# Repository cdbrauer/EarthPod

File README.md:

# EarthPod
Code for the [EarthPod](https://cdbrauer.github.io/research/index.html#earthpod) environmental sensor pod.

## Datalogging-Arduino

### Hardware

The code in this folder is intended to be used in a sensor pod based on a Adafruit Feather M0 Adalogger. Connected sensors include:

| Sensor | [V1](https://github.com/cdbrauer/EarthPod/tree/master/Datalogging-Arduino/feather-sensor-logging-v1) | [V2](https://github.com/cdbrauer/EarthPod/tree/master/Datalogging-Arduino/feather-sensor-logging-v2.1) |
| :------------- | :----------: | :-----------: |
| RTC | DS3231 | DS3231 |
| Gyroscope | FXAS21002C | FXAS21002C |
| Acclerometer/Magnetometer | FXOS8700 | FXOS8700 |
| Temperature/Humidity | si7021 | SHT21 |
| Air Pressure/Temperature | BME280 | BMP280 or SPL06-007 |
| Light Level | SI1145 | BH1750 |
| Wind Direction | TCS34725 | N/A |
| Wind Speed | Handheld Anemometer | N/A |

### feather-sensor-logging-v1

*Compatible with V1 only*

This program will create a .csv file on the Adalogger's SD card that records the measurements captured by the sensors. This program is only compatible with the Adafruit Feather M0 Adalogger, and will not fit on the Adafruit Feather 32u4 Adalogger due to memory constraints.

### feather-sensor-logging-v2.1

*Compatible with V2 Only*

This program will create a .csv file on the Adalogger's SD card that records the measurements captured by the sensors. This program is only compatible with the Adafruit Feather M0 Adalogger, and will not fit on the Adafruit Feather 32u4 Adalogger due to memory constraints.

### feather-sensor-tests/SPL06-007

Test I2C communication for an SPL06-007 air pressure and temperature sensor.

### feather-sensor-tests/anemometer

Test initialization and interrupts for a wind speed sensor from a [handheld anemometer](https://www.amazon.com/Anemometer-Velocity-Measurement-Thermometer-Windsurfing/dp/B01JOTJMU6/).

## Datalogging-Python

### Hardware

The code in this folder is intended to be used in a sensor pod based on a Raspberry Pi or Google Coral. The primary
sensing hardware is the Coral Environmental Sensor Board, which provides ambient light, barometric pressure, humidity, and temperature measurements. This board is compatible with both the Google Coral and Raspberry Pi. Additional sensors can be connected to the Environmental Sensor Board through a series of Grove connectors.

### enviro\_logging.py

This program will create a .csv file that records the measurements captured by the sensors in the Environmental Sensor
Board.

### enviro\_logging\_wind.py

This program adds functionality for reading wind speed using the sensor from a [handheld anemometer](https://www.amazon.com/Anemometer-Velocity-Measurement-Thermometer-Windsurfing/dp/B01JOTJMU6/).

### enviro\_logging\_wind\_airflow.py

This program adds functionality for reading wind speed using a [F662 Board Mount Airflow Sensor](https://www.degreec.com/pages/f660-662) from Degree Controls.

## MagnetRelease

### MagnetRelease.ino

Arduino program for the twist-release magnet system used to deploy the pod.

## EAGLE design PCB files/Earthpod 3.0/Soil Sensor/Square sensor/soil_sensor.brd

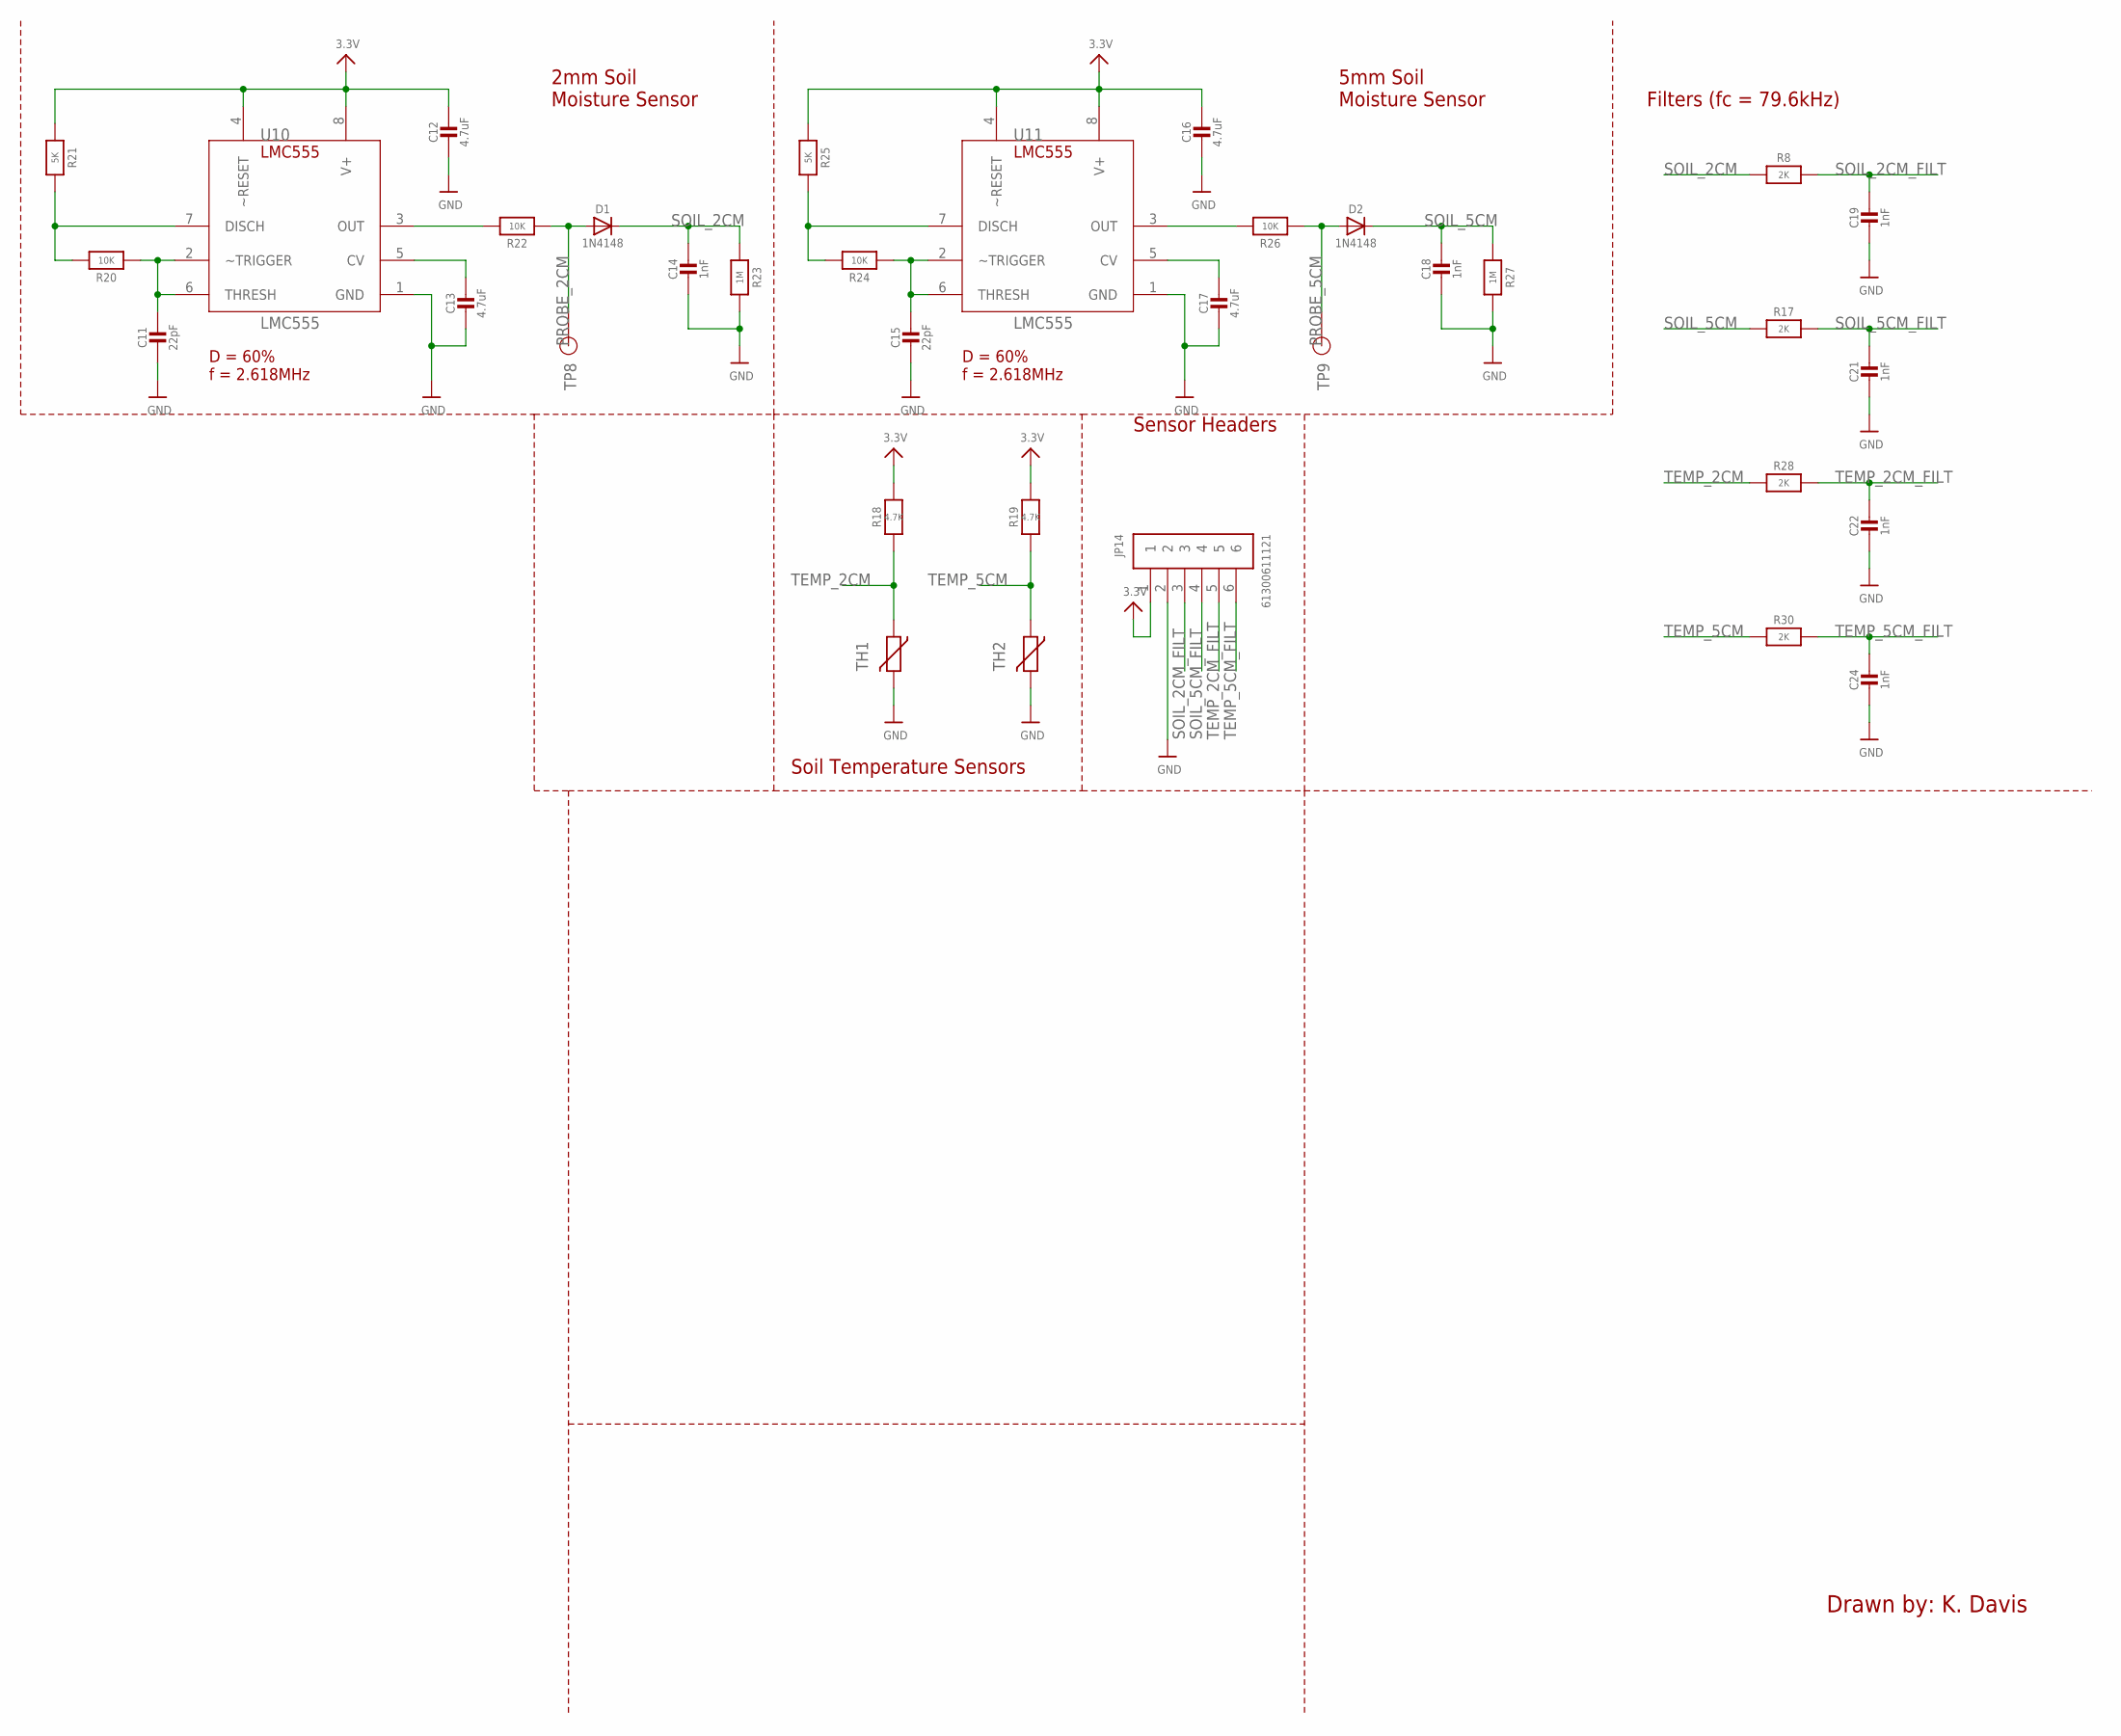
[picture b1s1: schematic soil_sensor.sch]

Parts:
C11, C15: 22pF; 0805-NO
C12, C13, C16, C17: 4.7uF; 0805-NO
C14, C18, C19, C21, C22, C24: 1nF; 0805-NO
D1, D2: 1N4148; SOD-323
JP14: 61300611121
R8, R17, R28, R30: 2K; 0603-NO
R18, R19: 4.7K; 0805-NO
R20, R22, R24, R26: 10K; 0805-NO
R21, R25: 5K; 0805-NO
R23, R27: 1M; 0805-NO
TH1, TH2: VARISTORCN1206; CT/CN1206
TP8, TP9: TP; TP_50MIL_CIRC
U10, U11: LMC555; SOIC-8

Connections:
3.3V: C12.1, C16.1, JP14.1, R18.2, R19.2, R21.1, R25.1, U10.4 (~RESET), U10.8 (V+), U11.4 (~RESET), U11.8 (V+)
FGD: C11.2, C12.2, C13.2, C14.2, C15.2, C16.2, C17.2, C18.2, C19.2, C21.2, C22.2, C24.2, JP14.2, R23.2, R27.2, TH1.2, TH2.2, U10.1 (GND), U11.1 (GND)
unnamed: C11.1, R20.1, U10.2 (~TRIGGER), U10.6 (THRESH)
unnamed: R20.2, R21.2, U10.7 (DISCH)
unnamed: C13.1, U10.5 (CV)
unnamed: C15.1, R24.1, U11.2 (~TRIGGER), U11.6 (THRESH)
unnamed: R24.2, R25.2, U11.7 (DISCH)
unnamed: R22.2, U10.3 (OUT)
unnamed: C17.1, U11.5 (CV)
unnamed: R26.2, U11.3 (OUT)
PROBE_2CM: D1.A, R22.1, TP8.1
PROBE_5CM: D2.A, R26.1, TP9.1
SOIL_2CM: C14.1, D1.C, R8.1, R23.1
SOIL_2CM_FILT: C19.1, JP14.3, R8.2
SOIL_5CM: C18.1, D2.C, R17.1, R27.1
SOIL_5CM_FILT: C21.1, JP14.4, R17.2
TEMP_2CM: R18.1, R28.1, TH1.1
TEMP_2CM_FILT: C22.1, JP14.5, R28.2
TEMP_5CM: R19.1, R30.1, TH2.1
TEMP_5CM_FILT: C24.1, JP14.6, R30.2

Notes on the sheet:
Soil Temperature Sensors
2mm Soil Moisture Sensor
5mm Soil Moisture Sensor
Filters (fc = 79.6kHz)
Drawn by: K. Davis
D = 60% f = 2.618MHz
Sensor Headers

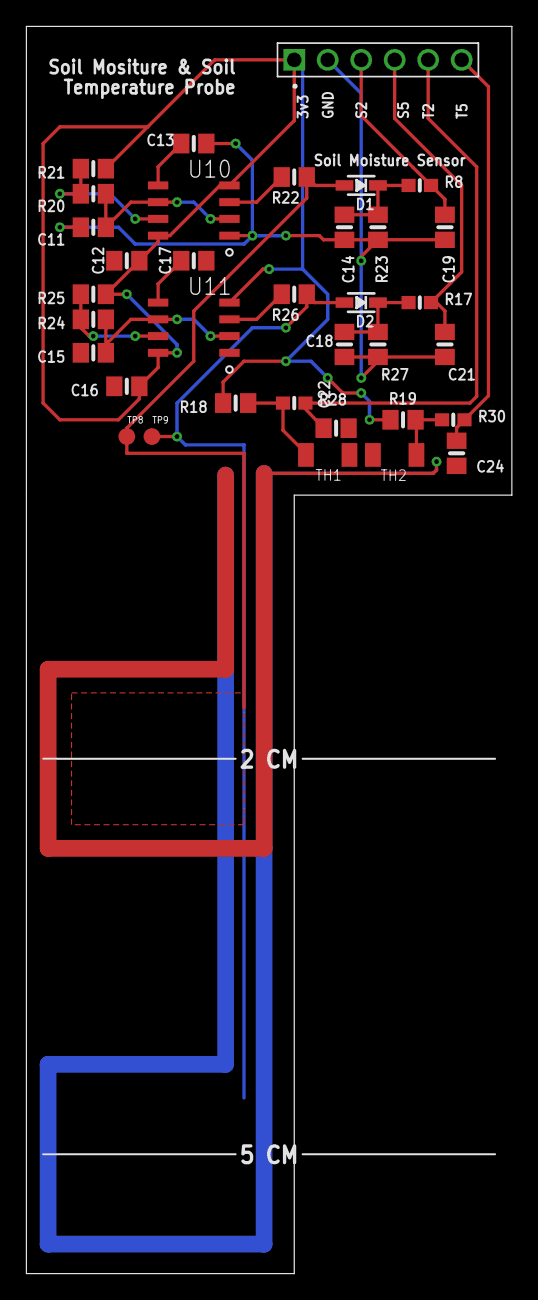
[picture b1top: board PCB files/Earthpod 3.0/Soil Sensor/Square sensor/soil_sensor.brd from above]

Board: 2 copper layers, 36.8 x 94.6 mm, 35 parts (0 on the bottom side), 20 nets.

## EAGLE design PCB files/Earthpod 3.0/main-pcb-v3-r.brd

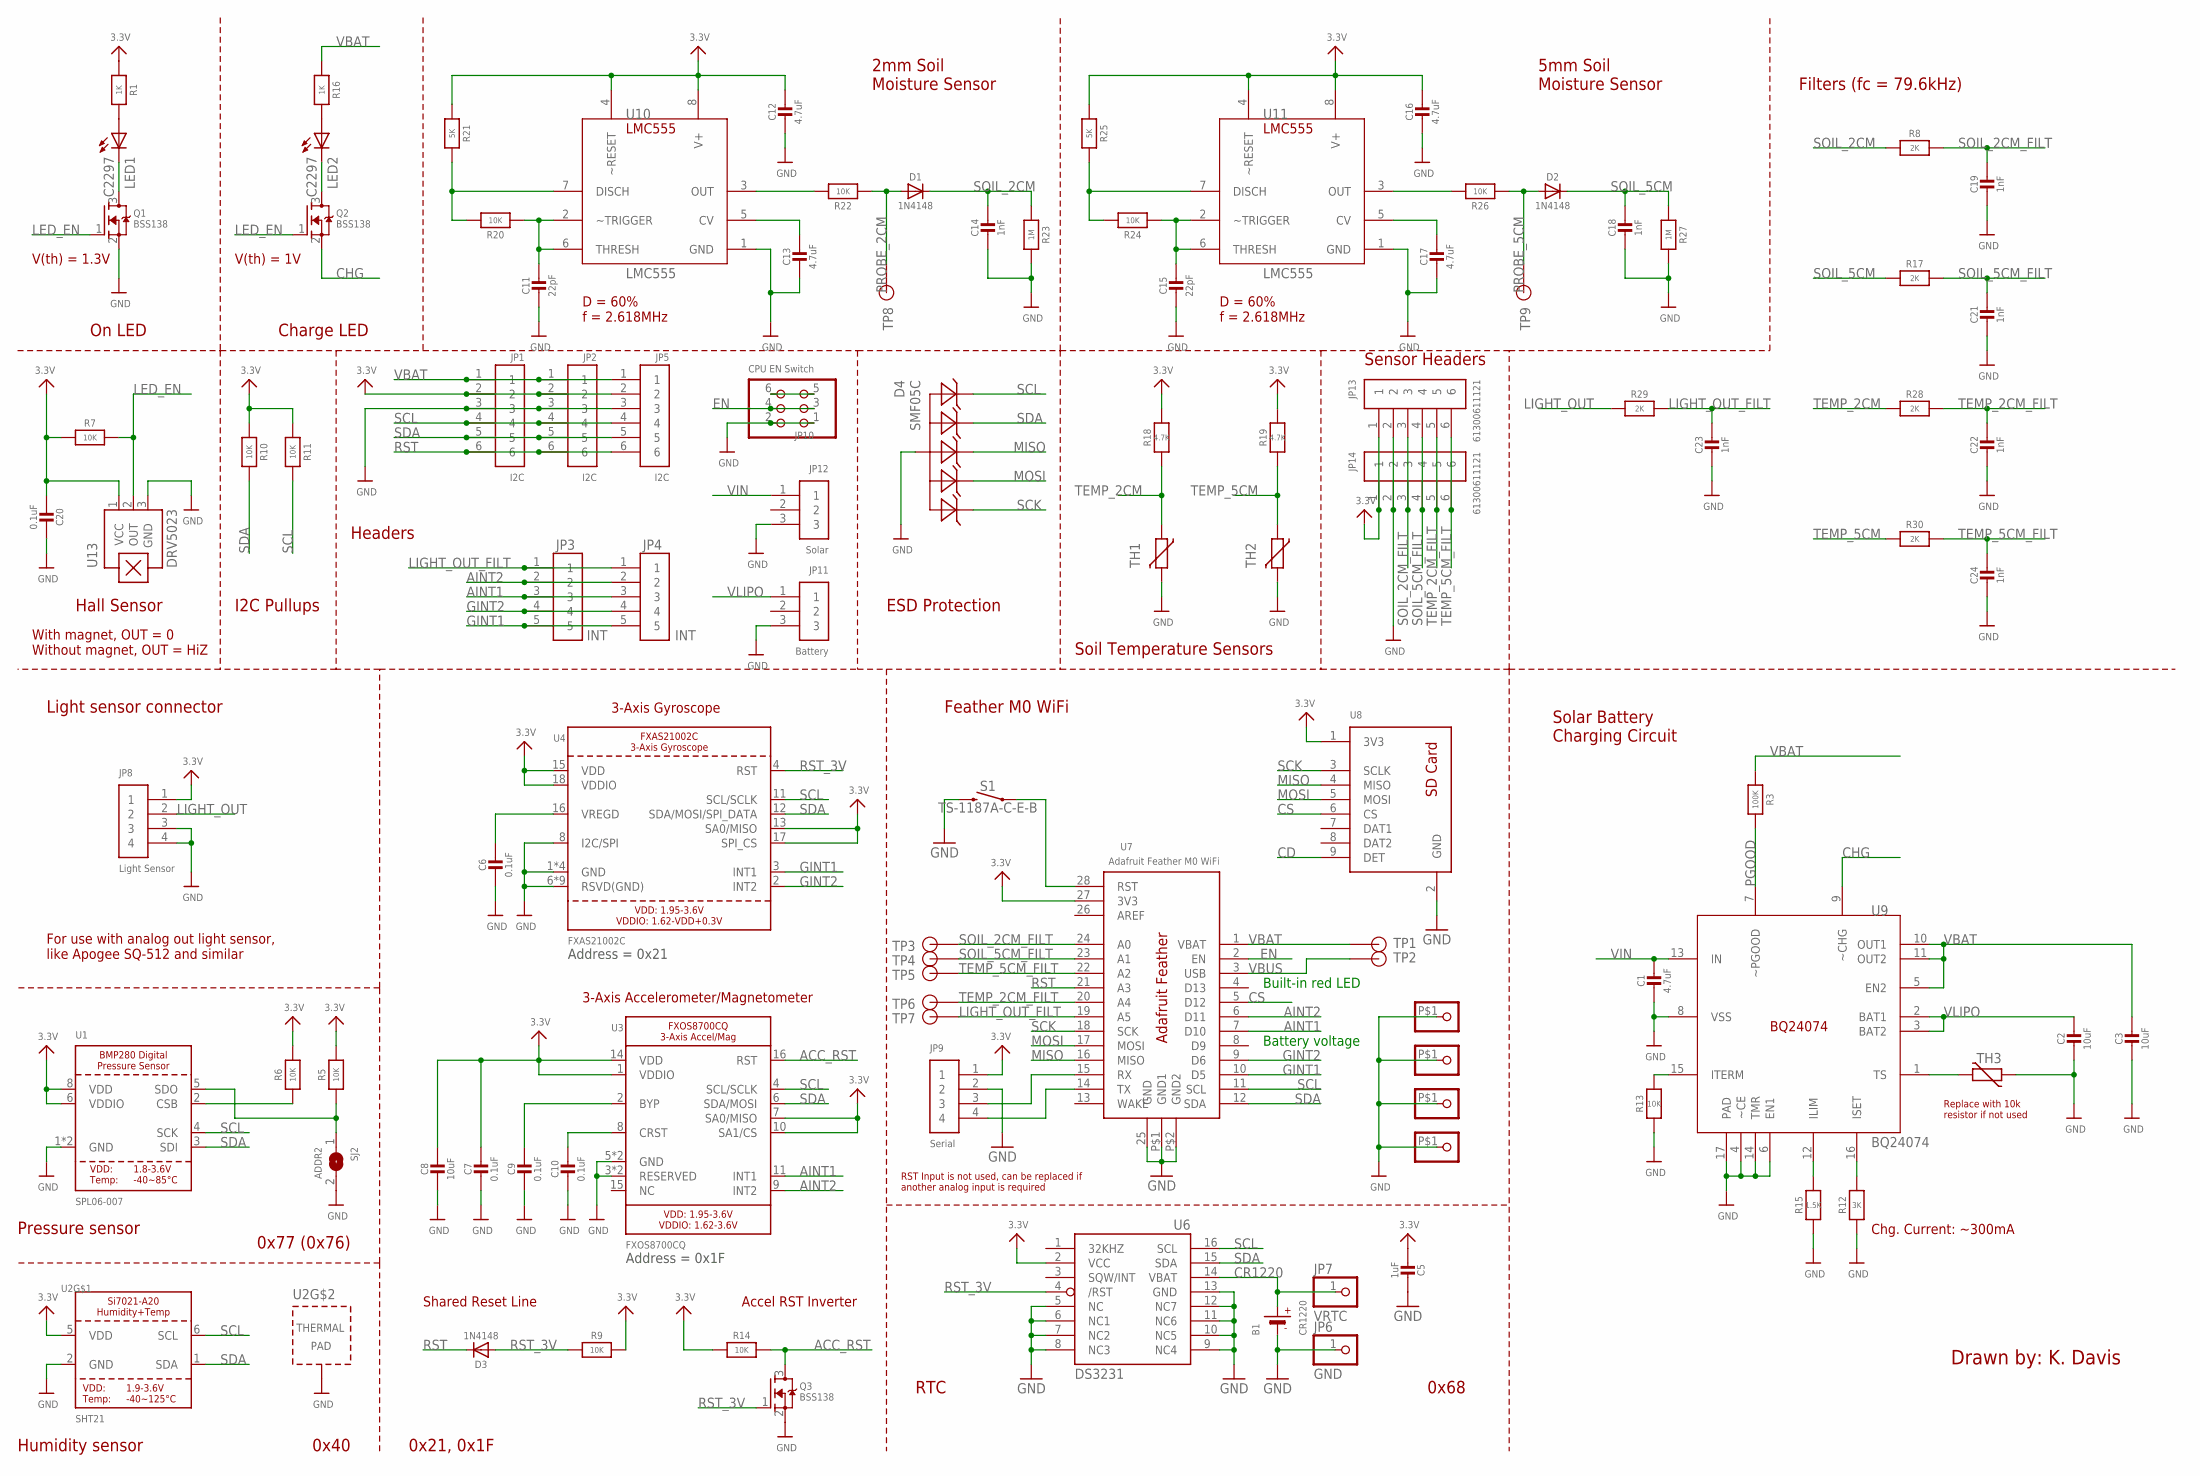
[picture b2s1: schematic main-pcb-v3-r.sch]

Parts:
B1: CR1220; CR1220-2
C1, C12, C13, C16, C17: 4.7uF; 0805-NO
C2, C3, C8: 10uF; 0805-NO
C5: 1uF; 0805-NO
C6, C7, C9, C10, C20: 0.1uF; 0805-NO
C11, C15: 22pF; 0805-NO
C14, C18, C19, C21, C22, C23, C24: 1nF; 0805-NO
D1, D2, D3: 1N4148; SOD-323
D4: SMF05C; SC70-6
JP1, JP2, JP5: I2C; 61300611121
JP3, JP4: INT; 61300511121
JP6: GND; 1X01_ROUND
JP7: VRTC; 1X01_ROUND
JP8: Light Sensor; 61300411121
JP9: Serial; 61300411121
JP10: CPU EN Switch; 2X03
JP11: Battery; 61300311121
JP12: Solar; 61300311121
JP13, JP14: 61300611121
LED1, LED2: C2297; CHIPLED_0805
Q1, Q2, Q3: BSS138; SOT23-WIDE
R1, R16: 1K; 0603-NO
R3: 100K; 0603-NO
R5, R6, R7, R10, R11: 10K; 0603-NO
R8, R17, R28, R29, R30: 2K; 0603-NO
R9, R13, R14, R20, R22, R24, R26: 10K; 0805-NO
R12: 3K; 0805-NO
R15: 1.5K; 0805-NO
R18, R19: 4.7K; 0805-NO
R21, R25: 5K; 0805-NO
R23, R27: 1M; 0805-NO
S1: TS-1187A-C-E-B; TACTILE_SWITCH_SMD_5.2MM
SJ2: ADDR2; SOLDERJUMPER_ARROW_NOPASTE
TH1, TH2, TH3: VARISTORCN1206; CT/CN1206
TP1, TP2, TP3, TP4, TP5, TP6, TP7, TP8, TP9: TP; TP_50MIL_CIRC
U1: SPL06-007; BMX280_COMBO
U2: SHT21; DFN6_3X3_SI
U3: FXOS8700CQ; QFN16_3MM_FREESCALE_5X3
U4: FXAS21002C; QFN24_4MM_FREESCALE_7X5
U6: DS3231/SO; SO16W
U7: Adafruit Feather M0 WiFi; FEATHER
U8: SDCARD2
U9: BQ24074; VQFN-16_3MM
U10, U11: LMC555; SOIC-8
U13: DRV5023; SOT-23
U$1, U$17, U$19, U$21: MOUNTING

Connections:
3.3V: C5.2, C7.1, C8.1, C12.1, C16.1, C20.2, JP1.2, JP2.2, JP5.2, JP8.1, JP9.1, JP13.1, JP14.1, R1.1, R5.2, R6.2, R7.1, R9.2, R10.1, R11.1, R14.1, R18.2, R19.2, R21.1, R25.1, U1.6 (VDDIO), U1.8 (VDD), U2.5 (VDD), U3.1 (VDDIO), U3.7 (SA0/MISO), U3.10 (SA1/CS), U3.14 (VDD), U4.13 (SA0/MISO), U4.15 (VDD), U4.17 (SPI_CS), U4.18 (VDDIO), U6.2 (VCC), U7.27 (3V3), U8.1 (3V3), U10.4 (~RESET), U10.8 (V+), U11.4 (~RESET), U11.8 (V+), U13.1 (VCC)
ACC_RST: Q3.3 (D), R14.2, U3.16 (RST)
AINT1: JP3.3, JP4.3, U3.11 (INT1), U7.7 (D10)
AINT2: JP3.2, JP4.2, U3.9 (INT2), U7.6 (D11)
CD: U8.9 (DET)
CHG: Q2.2 (S), U9.9 (~CHG)
CR1220: B1.+, JP7.1, U6.14 (VBAT)
CS: U7.5 (D12), U8.6 (CS)
EN: JP10.3, JP10.4, U7.2 (EN)
GINT1: JP3.5, JP4.5, U4.3 (INT1), U7.10 (D5)
GINT2: JP3.4, JP4.4, U4.2 (INT2), U7.9 (D6)
GND: B1.-, C1.2, C2.2, C3.2, C5.1, C6.2, C7.2, C8.2, C9.2, C10.2, C11.2, C12.2, C13.2, C14.2, C15.2, C16.2, C17.2, C18.2, C19.2, C20.1, C21.2, C22.2, C23.2, C24.2, D4.2 (A), JP1.3, JP2.3, JP5.3, JP6.1, JP8.3, JP8.4, JP9.2, JP10.1, JP10.2, JP11.3, JP12.3, JP13.2, JP14.2, Q1.2 (S), Q3.2 (S), R12.1, R13.1, R15.1, R23.2, R27.2, S1.3 (2), SJ2.2, TH1.2, TH2.2, TH3.2, U1.1 (GND), U1.7 (GND), U2.2 (GND), U2.PAD (TP), U3.3 (RESERVED), U3.5 (GND), U3.12 (GND), U3.13 (RESERVED), U4.1 (GND), U4.5 (GND), U4.6 (RSVD(GND)), U4.7 (RSVD(GND)), U4.8 (I2C/SPI), U4.9 (RSVD(GND)), U4.10 (RSVD(GND)), U4.14 (GND), U4.19 (GND), U4.20 (RSVD(GND)), U4.21 (RSVD(GND)), U4.22 (RSVD(GND)), U4.23 (RSVD(GND)), U4.24 (RSVD(GND)), U6.5 (NC), U6.6 (NC1), U6.7 (NC2), U6.8 (NC3), U6.9 (NC4), U6.10 (NC5), U6.11 (NC6), U6.12 (NC7), U6.13 (GND), U7.25 (GND), U7.P$1 (GND1), U7.P$2 (GND2), U8.2 (GND), U9.4 (~CE), U9.6 (EN1), U9.8 (VSS), U9.14 (TMR), U9.17 (PAD), U10.1 (GND), U11.1 (GND), U13.3 (GND), U$1.P$1, U$17.P$1, U$19.P$1, U$21.P$1
ITERM: R13.2, U9.15 (ITERM)
LED1: LED1.C, Q1.3 (D)
LED2: LED2.C, Q2.3 (D)
LED_EN: Q1.1 (G), Q2.1 (G), R7.2, U13.2 (OUT)
LIGHT_OUT: JP8.2, R29.1
LIGHT_OUT_FILT: C23.1, JP3.1, JP4.1, R29.2, TP7.1, U7.19 (A5)
MISO: D4.4 (C3), U7.16 (MISO), U8.4 (MISO)
MOSI: D4.5 (C4), U7.17 (MOSI), U8.5 (MOSI)
unnamed: LED1.A, R1.2
unnamed: R6.1, U1.2 (CSB)
unnamed: R5.1, SJ2.1, U1.5 (SDO)
unnamed: JP9.3, U7.15 (RX)
unnamed: JP10.5, JP10.6
unnamed: JP9.4, U7.14 (TX)
unnamed: TH3.1, U9.1 (TS)
unnamed: S1.1, U7.28 (RST)
unnamed: C11.1, R20.1, U10.2 (~TRIGGER), U10.6 (THRESH)
unnamed: LED2.A, R16.2
unnamed: R20.2, R21.2, U10.7 (DISCH)
unnamed: C13.1, U10.5 (CV)
unnamed: C15.1, R24.1, U11.2 (~TRIGGER), U11.6 (THRESH)
unnamed: R12.2, U9.16 (ISET)
unnamed: R15.2, U9.12 (ILIM)
unnamed: R24.2, R25.2, U11.7 (DISCH)
unnamed: R22.2, U10.3 (OUT)
unnamed: C17.1, U11.5 (CV)
unnamed: R26.2, U11.3 (OUT)
unnamed: C6.1, U4.16 (VREGD)
unnamed: C9.1, U3.2 (BYP)
unnamed: C10.1, U3.8 (CRST)
PGOOD: R3.2, U9.7 (~PGOOD)
PROBE_2CM: D1.A, R22.1, TP8.1
PROBE_5CM: D2.A, R26.1, TP9.1
RST: D3.C, JP1.6, JP2.6, JP5.6, U7.21 (A3)
RST_3V: D3.A, Q3.1 (G), R9.1, U4.4 (RST), U6.4 (/RST)
SCK: D4.6 (C5), U7.18 (SCK), U8.3 (SCLK)
SCL: D4.1 (C1), JP1.4, JP2.4, JP5.4, R11.2, U1.4 (SCK), U2.6 (SCL), U3.4 (SCL/SCLK), U4.11 (SCL/SCLK), U6.16 (SCL), U7.11 (SCL)
SDA: D4.3 (C2), JP1.5, JP2.5, JP5.5, R10.2, U1.3 (SDI), U2.1 (SDA), U3.6 (SDA/MOSI), U4.12 (SDA/MOSI/SPI_DATA), U6.15 (SDA), U7.12 (SDA)
SOIL_2CM: C14.1, D1.C, R8.1, R23.1
SOIL_2CM_FILT: C19.1, JP13.3, JP14.3, R8.2, TP3.1, U7.24 (A0)
SOIL_5CM: C18.1, D2.C, R17.1, R27.1
SOIL_5CM_FILT: C21.1, JP13.4, JP14.4, R17.2, TP4.1, U7.23 (A1)
TEMP_2CM: R18.1, R28.1, TH1.1
TEMP_2CM_FILT: C22.1, JP13.5, JP14.5, R28.2, TP6.1, U7.20 (A4)
TEMP_5CM: R19.1, R30.1, TH2.1
TEMP_5CM_FILT: C24.1, JP13.6, JP14.6, R30.2, TP5.1, U7.22 (A2)
VBAT: C3.1, JP1.1, JP2.1, JP5.1, R3.1, R16.1, TP1.1, U7.1 (VBAT), U9.5 (EN2), U9.10 (OUT1), U9.11 (OUT2)
VBUS: TP2.1, U7.3 (USB)
VIN: C1.1, JP12.1, U9.13 (IN)
VLIPO: C2.1, JP11.1, U9.2 (BAT1), U9.3 (BAT2)

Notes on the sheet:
I2C Pullups
Headers
On LED
RTC
0x68
ESD Protection
Battery voltage
Built-in red LED
Light sensor connector
Pressure sensor
Humidity sensor
0x40
0x77 (0x76)
Address = 0x21
Address = 0x1F
3-Axis Accelerometer/Magnetometer
3-Axis Gyroscope
Shared Reset Line
Accel RST Inverter
0x21, 0x1F
Chg. Current: ~300mA
Hall Sensor
Soil Temperature Sensors
Charge LED
2mm Soil Moisture Sensor
5mm Soil Moisture Sensor
Filters (fc = 79.6kHz)
Solar Battery Charging Circuit
Feather M0 WiFi
With magnet, OUT = 0 Without magnet, OUT = HiZ
V(th) = 1.3V
V(th) = 1V
Drawn by: K. Davis
D = 60% f = 2.618MHz
Replace with 10k resistor if not used
For use with analog out light sensor, like Apogee SQ-512 and similar
RST Input is not used, can be replaced if another analog input is required
Sensor Headers

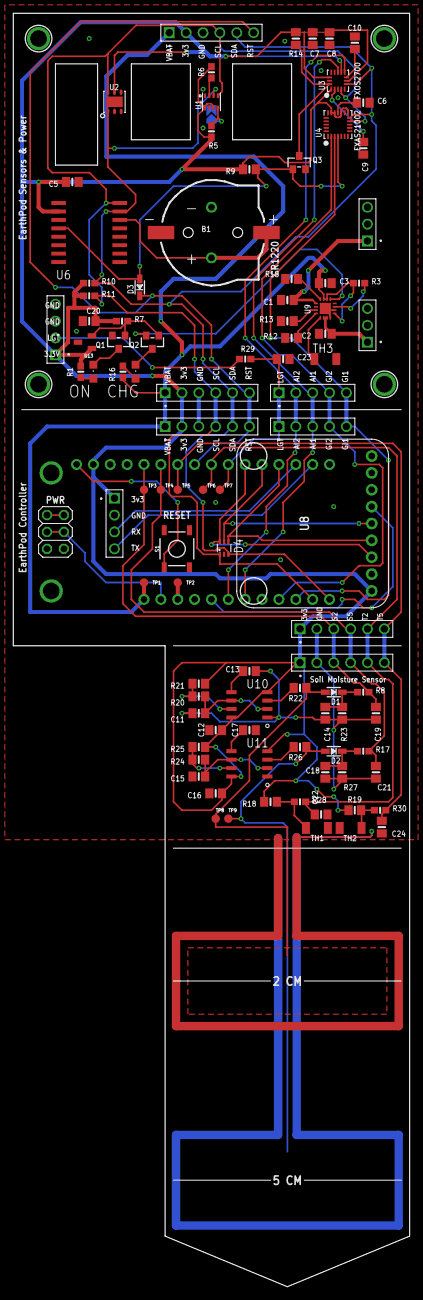
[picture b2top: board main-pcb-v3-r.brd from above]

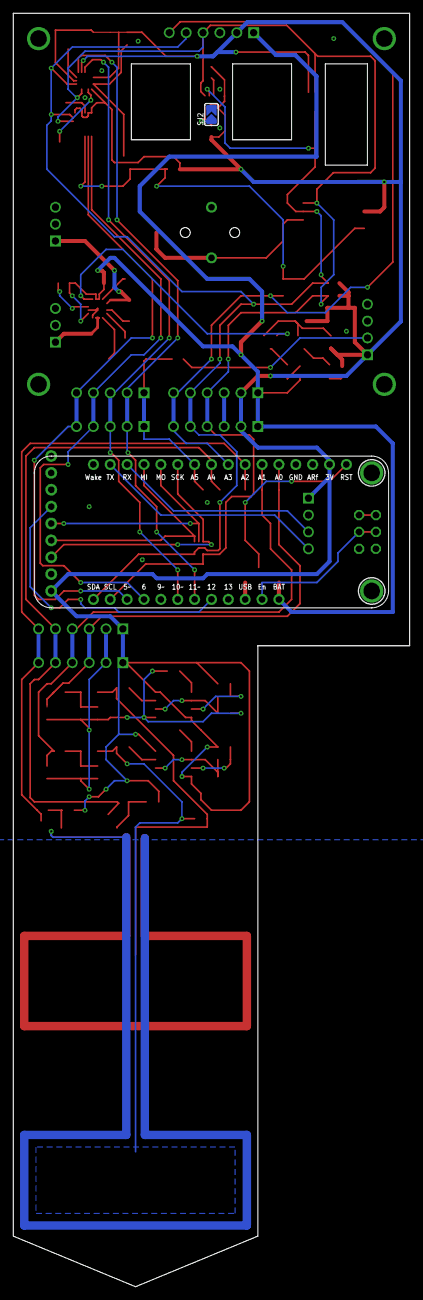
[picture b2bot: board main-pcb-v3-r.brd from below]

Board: 2 copper layers, 59.7 x 191.8 mm, 104 parts (2 on the bottom side), 61 nets.

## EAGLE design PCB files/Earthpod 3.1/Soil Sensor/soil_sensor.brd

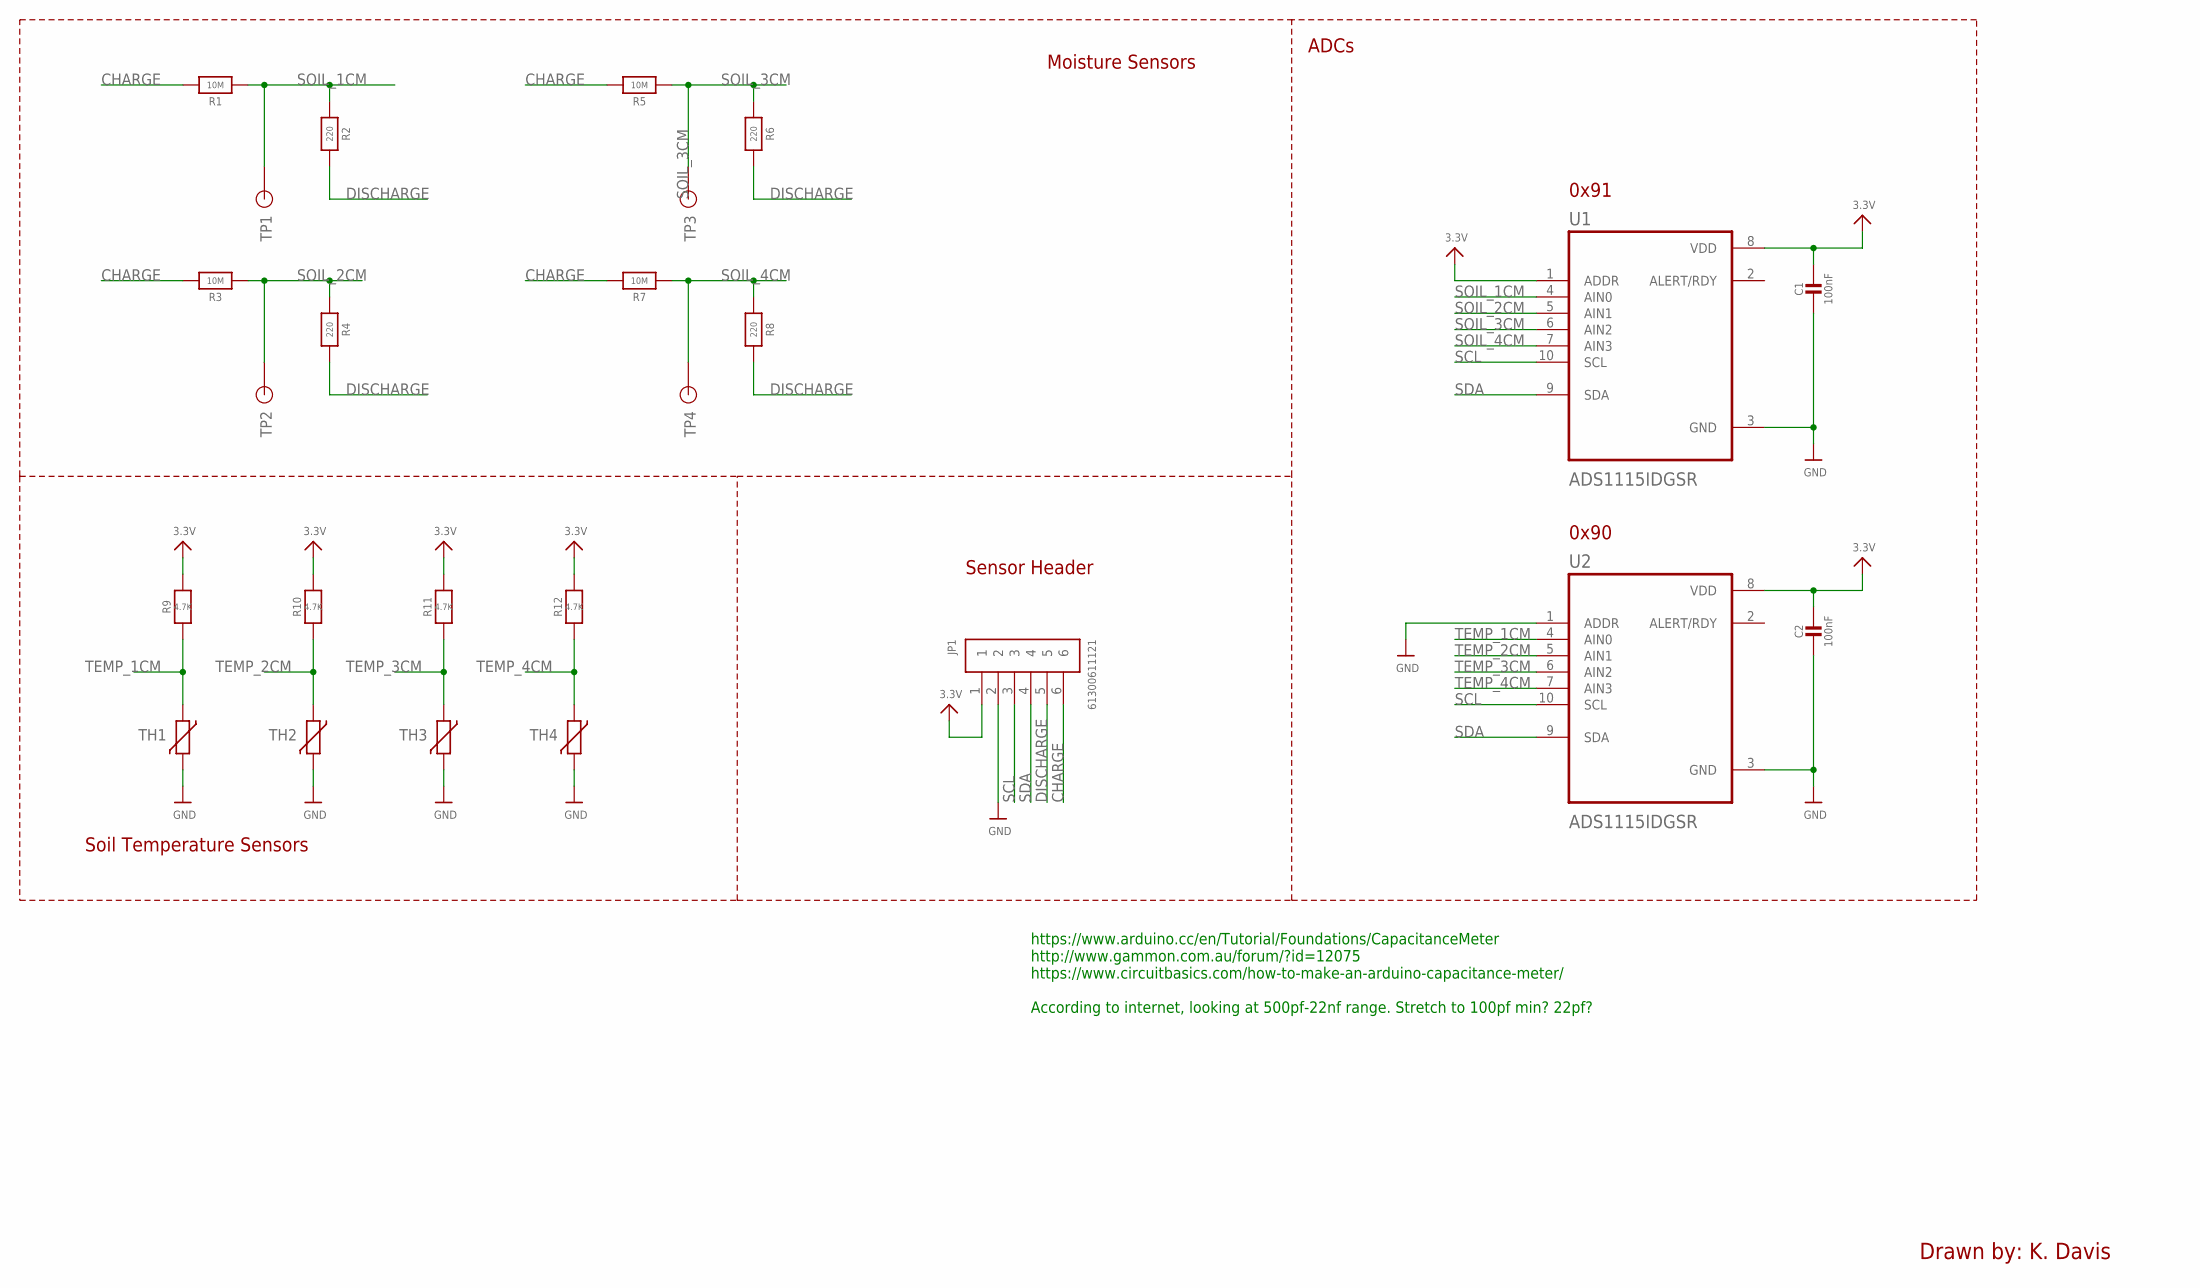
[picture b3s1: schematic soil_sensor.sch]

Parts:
C1, C2: 100nF; 0805-NO
JP1: 61300611121
R1, R3, R5, R7: 10M; 0805-NO
R2, R4, R6, R8: 220; 0805-NO
R9, R10, R11, R12: 4.7K; 0805-NO
TH1, TH2, TH3, TH4: VARISTORCN0805; CT/CN0805
TP1, TP2, TP3, TP4: TP; TP_50MIL_CIRC
U1, U2: ADS1115IDGSR; SOP50P490X110-10N

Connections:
3.3V: C1.1, C2.1, JP1.1, R9.2, R10.2, R11.2, R12.2, U1.1 (ADDR), U1.8 (VDD), U2.8 (VDD)
CHARGE: JP1.6, R1.2, R3.2, R5.2, R7.2
DISCHARGE: JP1.5, R2.2, R4.2, R6.2, R8.2
GND: C1.2, C2.2, JP1.2, TH1.2, TH2.2, TH3.2, TH4.2, U1.3 (GND), U2.1 (ADDR), U2.3 (GND)
SCL: JP1.3, U1.10 (SCL), U2.10 (SCL)
SDA: JP1.4, U1.9 (SDA), U2.9 (SDA)
SOIL_1CM: R1.1, R2.1, TP1.1, U1.4 (AIN0)
SOIL_2CM: R3.1, R4.1, TP2.1, U1.5 (AIN1)
SOIL_3CM: R5.1, R6.1, TP3.1, U1.6 (AIN2)
SOIL_4CM: R7.1, R8.1, TP4.1, U1.7 (AIN3)
TEMP_1CM: R9.1, TH1.1, U2.4 (AIN0)
TEMP_2CM: R10.1, TH2.1, U2.5 (AIN1)
TEMP_3CM: R11.1, TH3.1, U2.6 (AIN2)
TEMP_4CM: R12.1, TH4.1, U2.7 (AIN3)

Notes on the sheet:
Moisture Sensors
Sensor Header
Drawn by: K. Davis
https://www.arduino.cc/en/Tutorial/Foundations/CapacitanceMeter http://www.gammon.com.au/forum/?id=12075 https://www.circuitbasics.com/how-to-make-an-arduino-capacitance-meter/ According to internet, looking at 500pf-22nf range. Stretch to 100pf min? 22pf?
Soil Temperature Sensors
0x91
0x90
ADCs

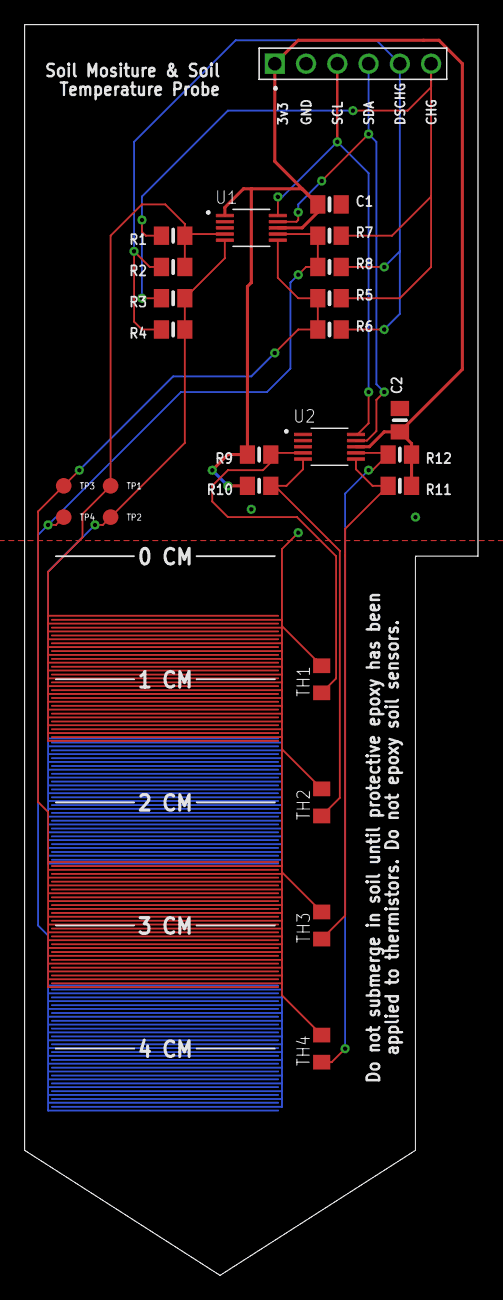
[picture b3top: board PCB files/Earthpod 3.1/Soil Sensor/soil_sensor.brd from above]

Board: 2 copper layers, 36.8 x 101.6 mm, 25 parts (0 on the bottom side), 14 nets.

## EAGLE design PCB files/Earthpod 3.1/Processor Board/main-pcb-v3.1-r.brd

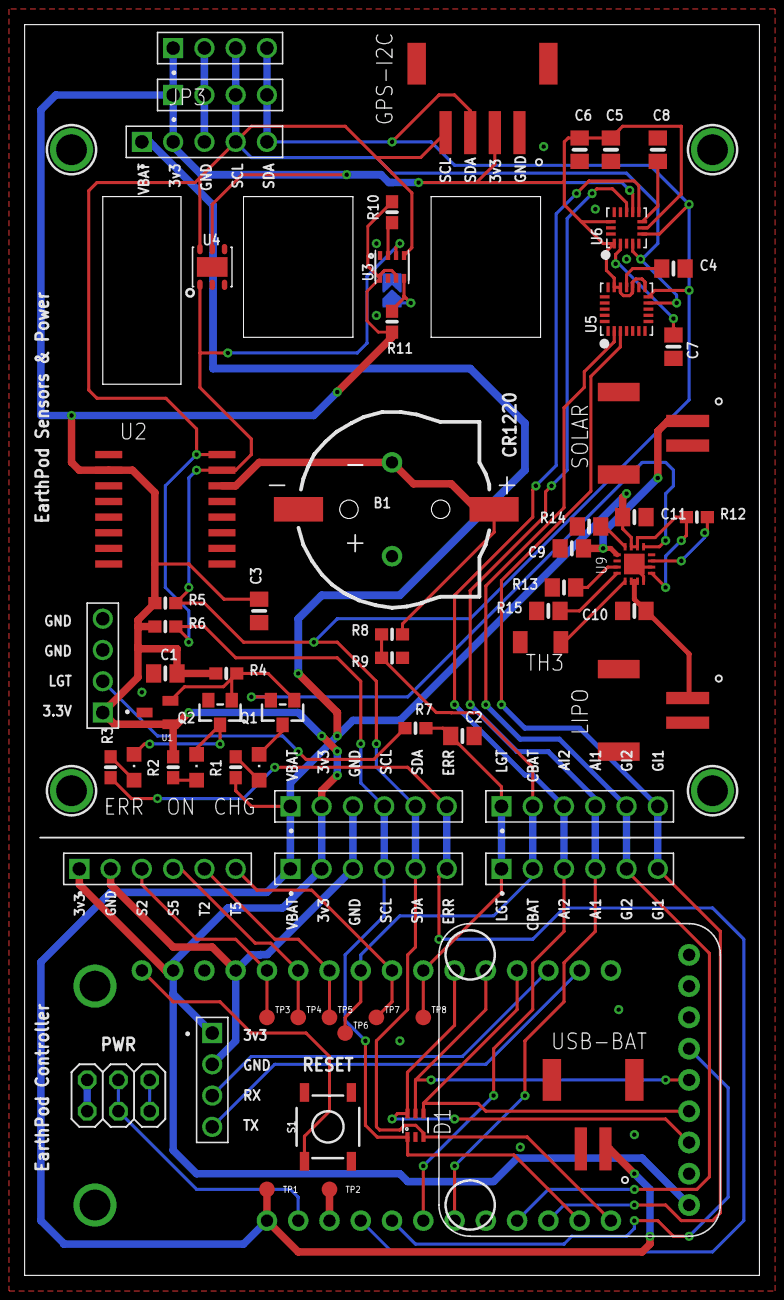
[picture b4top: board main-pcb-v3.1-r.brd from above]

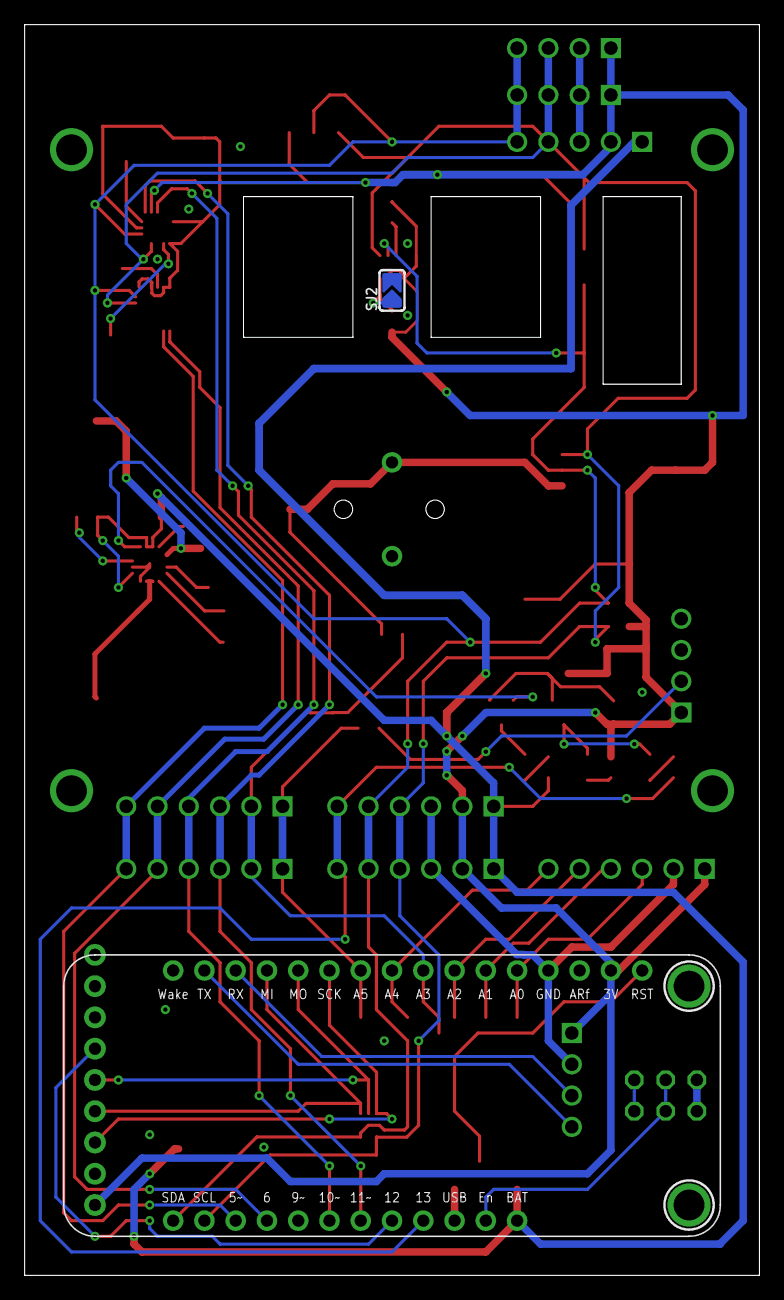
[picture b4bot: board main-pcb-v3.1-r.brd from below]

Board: 2 copper layers, 59.7 x 101.6 mm, 74 parts (2 on the bottom side), 47 nets.

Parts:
B1: CR1220; CR1220-2
C1, C4, C6, C7, C8: 0.1uF; 0805-NO
C2: 1nF; 0805-NO
C3: 1uF; 0805-NO
C5, C10, C11: 10uF; 0805-NO
C9: 4.7uF; 0805-NO
D1: SMF05C; SC70-6
JP1, JP2, JP9, JP10: I2C; 61300611121
JP3: I2C; 61300511121
JP4, JP5, JP13: I2C; 61300411121
JP6: Solar; JST-2
JP7: Battery; JST-2
JP8: GPS; JST-4
JP11: CPU EN Switch; 2X03
JP12: Soil; 61300611121
JP14: VRTC; 1X01_ROUND
JP15: GND; 1X01_ROUND
JP16: Serial; 61300411121
JP17: Charge over USB; JST-2
LED1, LED2: C2297; CHIPLED_0805
LED3: NCD0805R1; CHIPLED_0805
Q1, Q2: BSS138; SOT23-WIDE
R1, R2, R3: 1K; 0603-NO
R4, R5, R6, R8, R9, R10, R11: 10K; 0603-NO
R7: 2K; 0603-NO
R12: 100K; 0603-NO
R13: 10K; 0805-NO
R14: 1.5K; 0805-NO
R15: 3K; 0805-NO
S1: TS-1187A-C-E-B; TACTILE_SWITCH_SMD_5.2MM
SJ2: ADDR2; SOLDERJUMPER_ARROW_NOPASTE
TH3: CT/CN1206
TP1, TP2, TP3, TP4, TP5, TP6, TP7, TP8: TP; TP_50MIL_CIRC
U1: DRV5023; SOT-23
U2: DS3231/SO; SO16W
U3: SPL06-007; BMX280_COMBO
U4: SHT21; DFN6_3X3_SI
U5: FXAS21002C; QFN24_4MM_FREESCALE_7X5
U6: FXOS8700CQ; QFN16_3MM_FREESCALE_5X3
U7: Adafruit Feather M0 WiFi; FEATHER
U8: SDCARD2
U9: BQ24074; VQFN-16_3MM
U$1, U$17, U$19, U$21: MOUNTING

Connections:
3.3V: C1.2, C3.2, C5.1, C6.1, JP1.2, JP2.2, JP3.2, JP4.1, JP5.1, JP8.2, JP12.1, JP13.1, JP16.1, R2.1, R4.1, R5.1, R6.1, R10.2, R11.2, U1.1, U2.2, U3.6, U3.8, U4.5, U5.13, U5.15, U5.17, U5.18, U6.1, U6.7, U6.10, U6.14, U7.27, U8.1
AINT1: JP9.4, JP10.4, U6.11, U7.7
AINT2: JP9.3, JP10.3, U6.9, U7.6
CHG: Q1.2, U9.9
CLK_BAT_MON: JP9.2, JP10.2, R8.2, R9.1, TP6.1, U7.21
CR1220: B1.+, JP14.1, R8.1, U2.14
CS: U7.5, U8.6
EN: JP11.3, JP11.4, U7.2
GINT1: JP9.6, JP10.6, U5.3, U7.10
GINT2: JP9.5, JP10.5, U5.2, U7.9
GND: B1.-, C1.1, C2.2, C3.1, C4.2, C5.2, C6.2, C7.2, C8.2, C9.2, C10.2, C11.2, D1.2, JP1.3, JP2.3, JP3.3, JP4.2, JP5.2, JP6.2, JP7.2, JP8.1, JP11.1, JP11.2, JP12.2, JP13.3, JP13.4, JP15.1, JP16.2, JP17.2, Q2.2, R9.2, R13.1, R14.1, R15.1, S1.3, SJ2.2, TH3.2, U1.3, U2.5, U2.6, U2.7, U2.8, U2.9, U2.10, U2.11, U2.12, U2.13, U3.1, U3.7, U4.2, U4.PAD, U5.1, U5.5, U5.6, U5.7, U5.8, U5.9, U5.10, U5.14, U5.19, U5.20, U5.21, U5.22, U5.23, U5.24, U6.3, U6.5, U6.12, U6.13, U7.25, U7.P$1, U7.P$2, U8.2, U9.4, U9.6, U9.8, U9.14, U9.17, U$1.P$1, U$17.P$1, U$19.P$1, U$21.P$1
ITERM: R13.2, U9.15
LED1: LED1.C, Q1.3
LED_EN: Q1.1, Q2.1, R4.2, U1.2
LED_RED: JP1.6, JP2.6, R3.1, U7.4
LIGHT_OUT: JP13.2, R7.1
LIGHT_OUT_FILT: C2.1, JP9.1, JP10.1, R7.2, TP8.1, U7.19
MISO: D1.4, U7.16, U8.4
MOSI: D1.5, U7.17, U8.5
unnamed: LED2.A, R2.2
unnamed: LED3.A, R3.2
unnamed: R10.1, U3.2
unnamed: R11.1, SJ2.1, U3.5
unnamed: JP16.3, U7.15
unnamed: JP11.5, JP11.6
unnamed: JP16.4, U7.14
unnamed: TH3.1, U9.1
unnamed: S1.1, U7.28
unnamed: LED1.A, R1.2
unnamed: R15.2, U9.16
unnamed: R14.2, U9.12
unnamed: C4.1, U5.16
unnamed: C7.1, U6.2
unnamed: C8.1, U6.8
PGOOD: R12.2, U9.7
SCK: D1.6, U7.18, U8.3
SCL: D1.1, JP1.4, JP2.4, JP3.4, JP4.3, JP5.3, JP8.4, R6.2, U2.16, U3.4, U4.6, U5.11, U6.4, U7.11
SDA: D1.3, JP1.5, JP2.5, JP3.5, JP4.4, JP5.4, JP8.3, R5.2, U2.15, U3.3, U4.1, U5.12, U6.6, U7.12
SOIL_2CM_FILT: JP12.3, TP3.1, U7.24
SOIL_5CM_FILT: JP12.4, TP4.1, U7.23
STATUS_LEDS: LED2.C, LED3.C, Q2.3
TEMP_2CM_FILT: JP12.5, TP5.1, U7.22
TEMP_5CM_FILT: JP12.6, TP7.1, U7.20
VBAT: C11.1, JP1.1, JP2.1, JP3.1, JP17.1, R1.1, R12.1, TP1.1, U7.1, U9.5, U9.10, U9.11
VBUS: TP2.1, U7.3
VIN: C9.1, JP6.1, U9.13
VLIPO: C10.1, JP7.1, U9.2, U9.3

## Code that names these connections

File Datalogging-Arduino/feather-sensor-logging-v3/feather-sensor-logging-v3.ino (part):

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const int ADDR_GYRO = 0x21;

// Soil sensor pins
#define SOIL_2CM A0
#define SOIL_5CM A1
#define TEMP_2CM A4
#define TEMP_5CM A2
#define LIGHT_OUT A5

// SD card settings
bool sd_present = false;
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

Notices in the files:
parts and their libraries:
microbuilder: This work is placed in the public domain, and may be freely used for commercial and non-commercial work with the following conditions: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
SparkFun-Switches: Licensing: Creative Commons ShareAlike 4.0 International - https://creativecommons.org/licenses/by-sa/4.0
